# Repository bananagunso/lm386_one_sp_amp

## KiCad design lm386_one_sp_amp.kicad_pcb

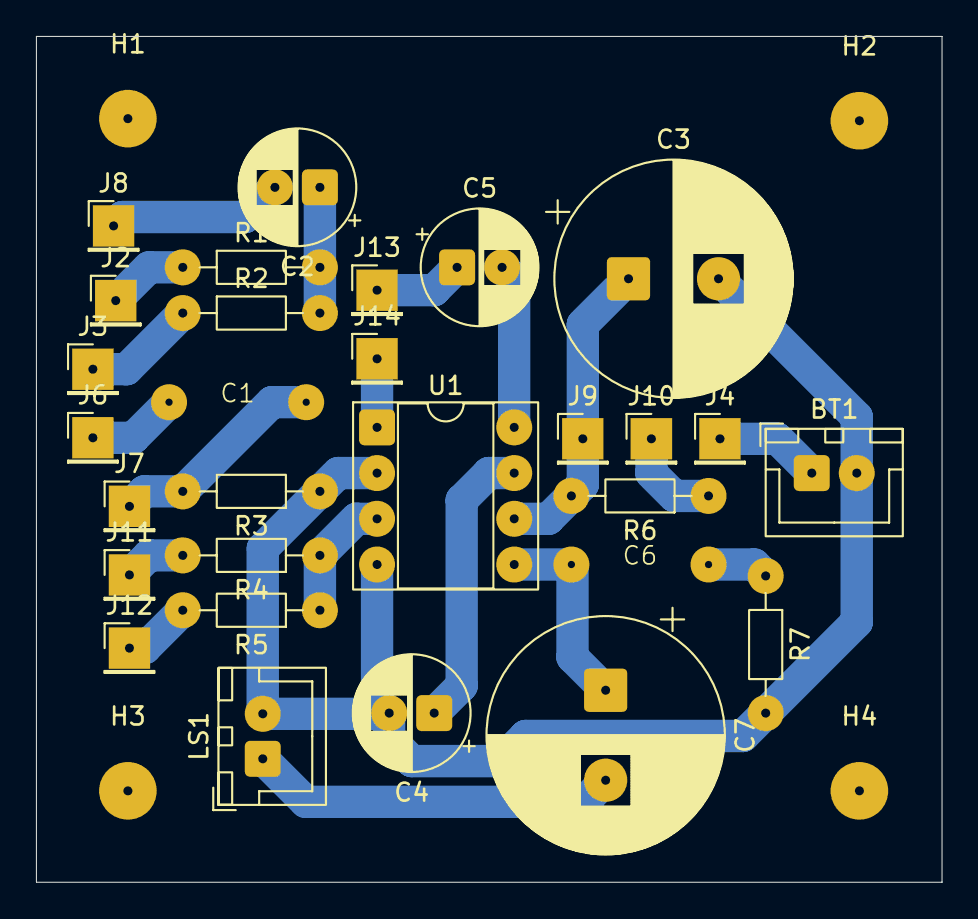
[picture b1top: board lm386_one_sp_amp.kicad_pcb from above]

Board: 2 copper layers, 50.3 x 47.0 mm, 33 parts (0 on the bottom side), 20 nets.

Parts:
BT1: Battery; JST_XH_B2B-XH-A_1x02_P2.50mm_Vertical
C1: 0.1uF; 11.6_7.0_p7.5
C2, C5: 10uF; CP_Radial_D6.3mm_P2.50mm
C3: 1000uF; CP_Radial_D13.0mm_P5.00mm
C4: 100uF; CP_Radial_D6.3mm_P2.50mm
C6: 0.047uF; 9.3_4.3_p7.5
C7: 2200uF; CP_Radial_D13.0mm_P5.00mm
H1, H2, H3, H4: MountingHole; MountingHole_3.2mm_M3
J2: IN1; PinHeader_1x01_P2.54mm_Vertical
J3: IN2; PinHeader_1x01_P2.54mm_Vertical
J4: ToSW; PinHeader_1x01_P2.54mm_Vertical
J6: IN3; PinHeader_1x01_P2.54mm_Vertical
J7: VR2_1; PinHeader_1x01_P2.54mm_Vertical
J8: VR1_1; PinHeader_1x01_P2.54mm_Vertical
J9: FromSW; PinHeader_1x01_P2.54mm_Vertical
J10: ToLED; PinHeader_1x01_P2.54mm_Vertical
J11: VR1_2; PinHeader_1x01_P2.54mm_Vertical
J12: VR2_2; PinHeader_1x01_P2.54mm_Vertical
J13: VR3_1; PinHeader_1x01_P2.54mm_Vertical
J14: VR3_3; PinHeader_1x01_P2.54mm_Vertical
LS1: Speaker; JST_XH_B2B-XH-A_1x02_P2.50mm_Vertical
R1, R2, R4, R5: 4.7k; R_Axial_DIN0204_L3.6mm_D1.6mm_P7.62mm_Horizontal
R3: 1M; R_Axial_DIN0204_L3.6mm_D1.6mm_P7.62mm_Horizontal
R6: 1.5k; R_Axial_DIN0204_L3.6mm_D1.6mm_P7.62mm_Horizontal
R7: 10; R_Axial_DIN0204_L3.6mm_D1.6mm_P7.62mm_Horizontal
U1: LM386; DIP-8_W7.62mm_Socket

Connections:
GND: BT1.2 (-), C3.2, C4.2, LS1.2, R3.1, R7.2, U1.2 (-), U1.4 (GND)
unnamed: BT1.1 (+), J4.1 (Pin_1_1)
unnamed: C2.1, R1.2, R2.2
unnamed: C5.2, U1.8 (GAIN)
unnamed: C6.1, C7.1, U1.5
unnamed: C6.2, R7.1
unnamed: C7.2, LS1.1
unnamed: J10.1 (Pin_1_1), R6.1
unnamed: J2.1 (Pin_1_1), R1.1
unnamed: J3.1 (Pin_1_1), R2.1
unnamed: C1.1, J6.1 (Pin_1_1)
unnamed: C1.2, J7.1 (Pin_1_1), R3.2
unnamed: C2.2, J8.1 (Pin_1_1)
unnamed: C3.1, J9.1 (Pin_1_1), R6.2, U1.6 (V+)
unnamed: J11.1 (Pin_1_1), R4.2
unnamed: J12.1 (Pin_1_1), R5.2
unnamed: C5.1, J13.1 (Pin_1_1)
unnamed: J14.1 (Pin_1_1), U1.1 (GAIN)
unnamed: R4.1, R5.1, U1.3 (+)
unnamed: C4.1, U1.7 (BYPASS)

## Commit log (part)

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2025-10-24 Initial
